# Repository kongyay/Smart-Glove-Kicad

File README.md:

# Glove2Gesture

the coolest project of 54D

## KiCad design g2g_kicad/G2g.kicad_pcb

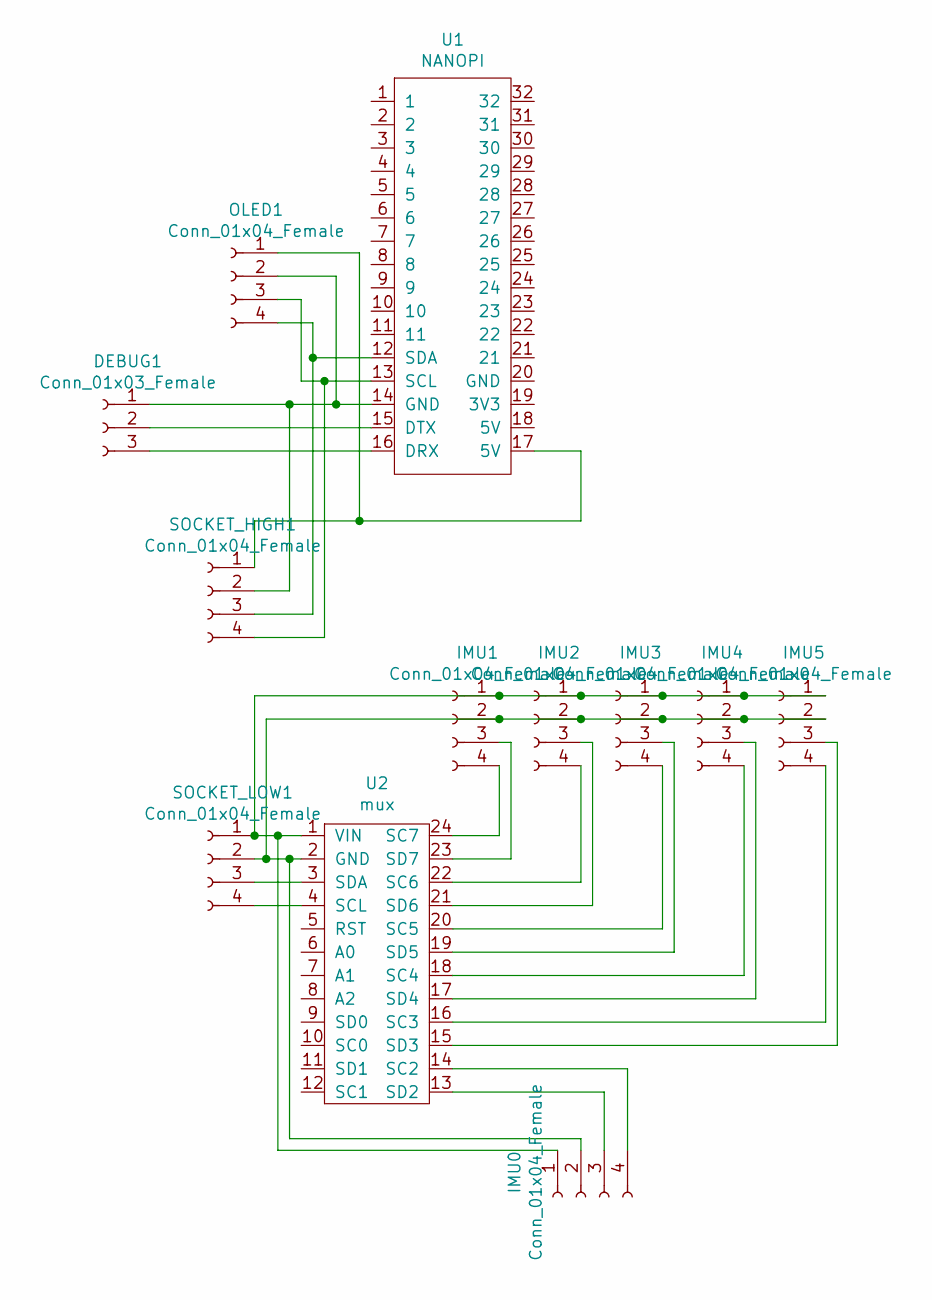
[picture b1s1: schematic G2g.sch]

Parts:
DEBUG1: Conn_01x03_Female; PinHeader_1x03_P2.54mm_Vertical
IMU0: Conn_01x04_Female; PinHeader_1x04_P2.54mm_Vertical
IMU1, IMU2, IMU3, IMU4, IMU5: Conn_01x04_Female; PinHeader_1x04_P2.00mm_Vertical
OLED1: Conn_01x04_Female; PinHeader_1x04_P2.54mm_Vertical
SOCKET_HIGH1: Conn_01x04_Female; PinHeader_1x04_P2.54mm_Vertical
SOCKET_LOW1: Conn_01x04_Female; PinHeader_1x04_P2.54mm_Vertical
U1: NANOPI; PinHeader_1x16_P2.54mm_Vertical
U2: mux; 1x12

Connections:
unnamed: DEBUG1.1, OLED1.2, SOCKET_HIGH1.2, U1.14 (GND)
unnamed: DEBUG1.2, U1.15 (DTX)
unnamed: DEBUG1.3, U1.16 (DRX)
unnamed: IMU0.1, IMU1.1, IMU2.1, IMU3.1, IMU4.1, IMU5.1, SOCKET_LOW1.1, U2.1 (VIN)
unnamed: IMU0.2, IMU1.2, IMU2.2, IMU3.2, IMU4.2, IMU5.2, SOCKET_LOW1.2, U2.2 (GND)
unnamed: IMU0.3, U2.13 (SD2)
unnamed: IMU0.4, U2.14 (SC2)
unnamed: IMU1.3, U2.23 (SD7)
unnamed: IMU1.4, U2.24 (SC7)
unnamed: IMU2.3, U2.21 (SD6)
unnamed: IMU2.4, U2.22 (SC6)
unnamed: IMU3.3, U2.19 (SD5)
unnamed: IMU3.4, U2.20 (SC5)
unnamed: IMU4.3, U2.17 (SD4)
unnamed: IMU4.4, U2.18 (SC4)
unnamed: IMU5.3, U2.15 (SD3)
unnamed: IMU5.4, U2.16 (SC3)
unnamed: OLED1.1, SOCKET_HIGH1.1, U1.17 (5V)
unnamed: OLED1.3, SOCKET_HIGH1.4, U1.13 (SCL)
unnamed: OLED1.4, SOCKET_HIGH1.3, U1.12 (SDA)
unnamed: SOCKET_LOW1.3, U2.3 (SDA)
unnamed: SOCKET_LOW1.4, U2.4 (SCL)

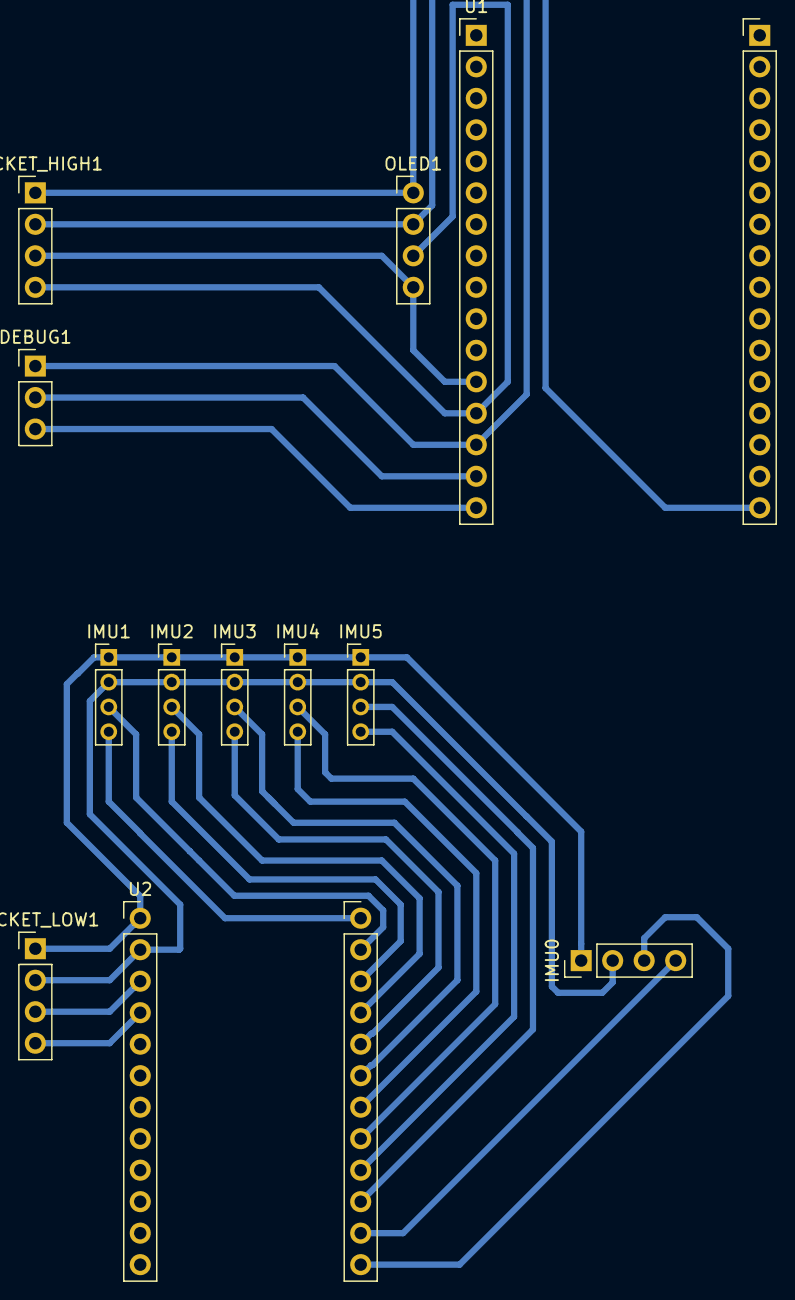
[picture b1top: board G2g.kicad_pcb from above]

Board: 2 copper layers, 12 parts (0 on the bottom side), 22 nets.

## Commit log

2018-09-05 init python
2018-09-05 some arduino tests
2018-09-05 serial comm
2018-09-26 add firmwares
2018-09-26 add just snapshot firmware only
2018-09-26 Revert "add firmwares"
    This reverts commit 73d3f8b36d991ff3d1fc3d3a90e903aec8d59c7c.
2018-09-26 add just snapshot again
2018-09-27 add origin firmware + openwrt15-node4 firmware
2018-10-08 Archive all Linkit related stuff / Add Flask threading/io server + client
2018-10-09 all original/custom-built linkit smart 7866 duo images, good luck :)
2018-10-28 implement MUX part
2018-10-30 add RNN predict
2018-10-30 add allIMU front / add predict page + auto
2018-11-16 Use Complementary angle
2018-12-18 start NW part
2018-12-27 [Add] Gesture Matching
2019-01-17 before change to raw data
2019-01-24 [Rework] Gesture Setting
2019-02-23 Predict with prob.
2019-02-23 Kicad
2019-02-23 Kicad only
2019-02-24 Increase heiht
2019-03-04 Add Nut bolt holes
